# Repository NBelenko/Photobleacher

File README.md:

# Photobleacher

Photobleacher is an open-source photobleaching device designed to bleach autofluorescence and pigments in biological materials. For more details about the project, please refer to our [publication](https://doi.org/10.1101/2025.02.24.639965).

## About This Repository

This repository contains the following materials.

1. CAD file of the chassis (Enclosure CAD)
2. PCB board design (PCB)
3. Sample stage design (Sample Stage)
4. List of components (Main BOM.xlsx)
5. Wiring diagram (PB Block & Wiring Diagram.pdf)
6. Assembly instructions (PB_Assembly Instructions.pdf)

## Citation

> Murakami et al. Open-source Photobleacher for Fluorescent Imaging of Large Pigment-Rich Tissues. bioRxiv (2025) https://doi.org/10.1101/2025.02.24.639965 

## License

We provide this open source software without any warranty under the [MIT license](https://opensource.org/licenses/MIT).

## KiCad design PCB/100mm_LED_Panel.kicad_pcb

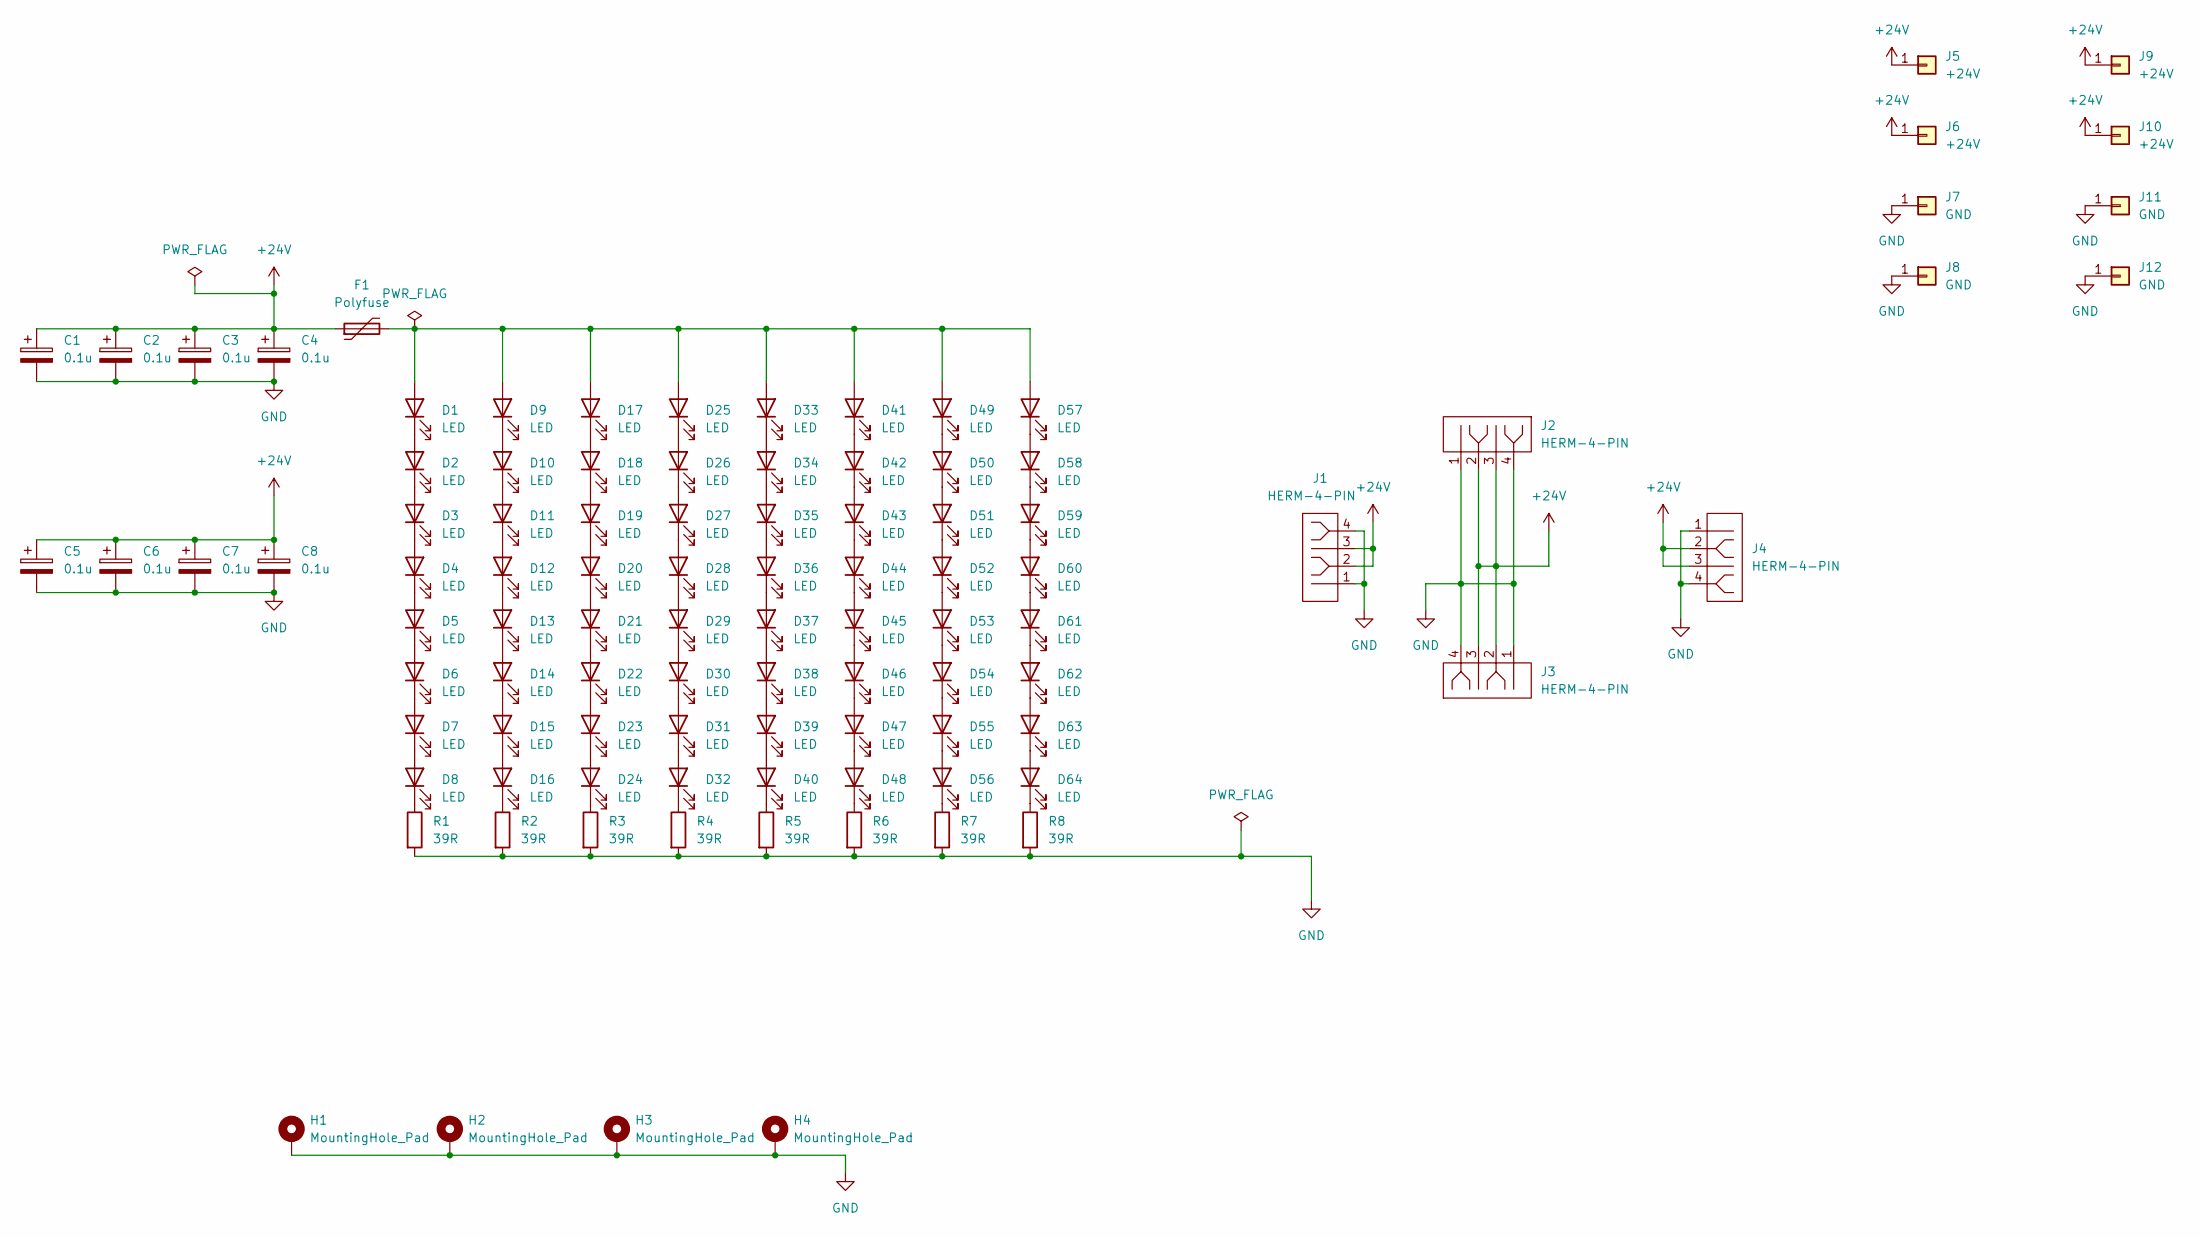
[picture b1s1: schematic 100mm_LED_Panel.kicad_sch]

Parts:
C1, C2, C3, C4, C5, C6, C7, C8: 0.1u; CP_EIA-3216-18_Kemet-A; Part Num T491A104K035AT; DigiKey P/N 399-3676-1-ND
D1, D2, D3, D4, D5, D6, D7, D8, D9, D10, D11, D12, D13, D14, D15, D16, D17, D18, D19, D20, D21, D22, D23, D24, D25, D26, D27, D28, D29, D30, D31, D32, D33, D34, D35, D36, D37, D38, D39, D40, D41, D42, D43, D44, D45, D46, D47, D48, D49, D50, D51, D52, D53, D54, D55, D56, D57, D58, D59, D60, D61, D62, D63, D64: LED; LED_Luminus_MP-3030-1100_3.0x3.0mm_Thermal-Vias; Part Num MP-3030-120H-30-80; DigiKey P/N 1214-MP-3030-120H-30-80CT-ND
F1: Polyfuse; Fuse_2018_5045Metric_Pad_HandSolder; Part Num DECASMDC050F/60-2; DigiKey P/N DECASMDC050F/60-2CT-ND
H1, H2, H3, H4: MountingHole_Pad; MountingHole_3.2mm_M3_Pad
J1, J2, J3, J4: HERM-4-PIN; TE 2213611-2 4 Position Mini-HERM; Part Num 2213611-2; DigiKey P/N A124894CT-ND
J5, J6, J9, J10: +24V; Faston .25 Tab; Part Num 63824-1; DigiKey P/N A29938CT-ND
J7, J8, J11, J12: GND; Faston .25 Tab; Part Num 63824-1; DigiKey P/N A29938CT-ND
R1, R2, R3, R4, R5, R6, R7, R8: 39R; R_1206_3216Metric_Pad1.30x1.75mm_HandSolder; Part Num RCS120639R0FKEA; DigiKey P/N 541-10632-1-ND

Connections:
+24V: C1.1, C2.1, C3.1, C4.1, C5.1, C6.1, C7.1, C8.1, F1.1, J1.2, J1.3, J2.2, J2.3, J3.2, J3.3, J4.2, J4.3, J5.1, J6.1, J9.1, J10.1
GND: C1.2, C2.2, C3.2, C4.2, C5.2, C6.2, C7.2, C8.2, H1.1, H2.1, H3.1, H4.1, J1.1, J1.4, J2.1, J2.4, J3.1, J3.4, J4.1, J4.4, J7.1, J8.1, J11.1, J12.1, R1.2, R2.2, R3.2, R4.2, R5.2, R6.2, R7.2, R8.2
unnamed: D1.1 (K), D2.2 (A)
unnamed: D1.2 (A), D9.2 (A), D17.2 (A), D25.2 (A), D33.2 (A), D41.2 (A), D49.2 (A), D57.2 (A), F1.2
unnamed: D2.1 (K), D3.2 (A)
unnamed: D3.1 (K), D4.2 (A)
unnamed: D4.1 (K), D5.2 (A)
unnamed: D5.1 (K), D6.2 (A)
unnamed: D6.1 (K), D7.2 (A)
unnamed: D7.1 (K), D8.2 (A)
unnamed: D8.1 (K), R1.1
unnamed: D10.1 (K), D11.2 (A)
unnamed: D9.1 (K), D10.2 (A)
unnamed: D11.1 (K), D12.2 (A)
unnamed: D12.1 (K), D13.2 (A)
unnamed: D13.1 (K), D14.2 (A)
unnamed: D14.1 (K), D15.2 (A)
unnamed: D15.1 (K), D16.2 (A)
unnamed: D16.1 (K), R2.1
unnamed: D17.1 (K), D18.2 (A)
unnamed: D18.1 (K), D19.2 (A)
unnamed: D19.1 (K), D20.2 (A)
unnamed: D20.1 (K), D21.2 (A)
unnamed: D21.1 (K), D22.2 (A)
unnamed: D22.1 (K), D23.2 (A)
unnamed: D23.1 (K), D24.2 (A)
unnamed: D24.1 (K), R3.1
unnamed: D25.1 (K), D26.2 (A)
unnamed: D26.1 (K), D27.2 (A)
unnamed: D27.1 (K), D28.2 (A)
unnamed: D28.1 (K), D29.2 (A)
unnamed: D29.1 (K), D30.2 (A)
unnamed: D30.1 (K), D31.2 (A)
unnamed: D31.1 (K), D32.2 (A)
unnamed: D32.1 (K), R4.1
unnamed: D33.1 (K), D34.2 (A)
unnamed: D34.1 (K), D35.2 (A)
unnamed: D35.1 (K), D36.2 (A)
unnamed: D36.1 (K), D37.2 (A)
unnamed: D37.1 (K), D38.2 (A)
unnamed: D38.1 (K), D39.2 (A)
unnamed: D39.1 (K), D40.2 (A)
unnamed: D40.1 (K), R5.1
unnamed: D41.1 (K), D42.2 (A)
unnamed: D42.1 (K), D43.2 (A)
unnamed: D43.1 (K), D44.2 (A)
unnamed: D44.1 (K), D45.2 (A)
unnamed: D45.1 (K), D46.2 (A)
unnamed: D46.1 (K), D47.2 (A)
unnamed: D47.1 (K), D48.2 (A)
unnamed: D48.1 (K), R6.1
unnamed: D49.1 (K), D50.2 (A)
unnamed: D50.1 (K), D51.2 (A)
unnamed: D51.1 (K), D52.2 (A)
unnamed: D52.1 (K), D53.2 (A)
unnamed: D53.1 (K), D54.2 (A)
unnamed: D54.1 (K), D55.2 (A)
unnamed: D55.1 (K), D56.2 (A)
unnamed: D56.1 (K), R7.1
unnamed: D57.1 (K), D58.2 (A)
unnamed: D58.1 (K), D59.2 (A)
unnamed: D59.1 (K), D60.2 (A)
unnamed: D60.1 (K), D61.2 (A)
unnamed: D61.1 (K), D62.2 (A)
unnamed: D62.1 (K), D63.2 (A)
unnamed: D63.1 (K), D64.2 (A)
unnamed: D64.1 (K), R8.1

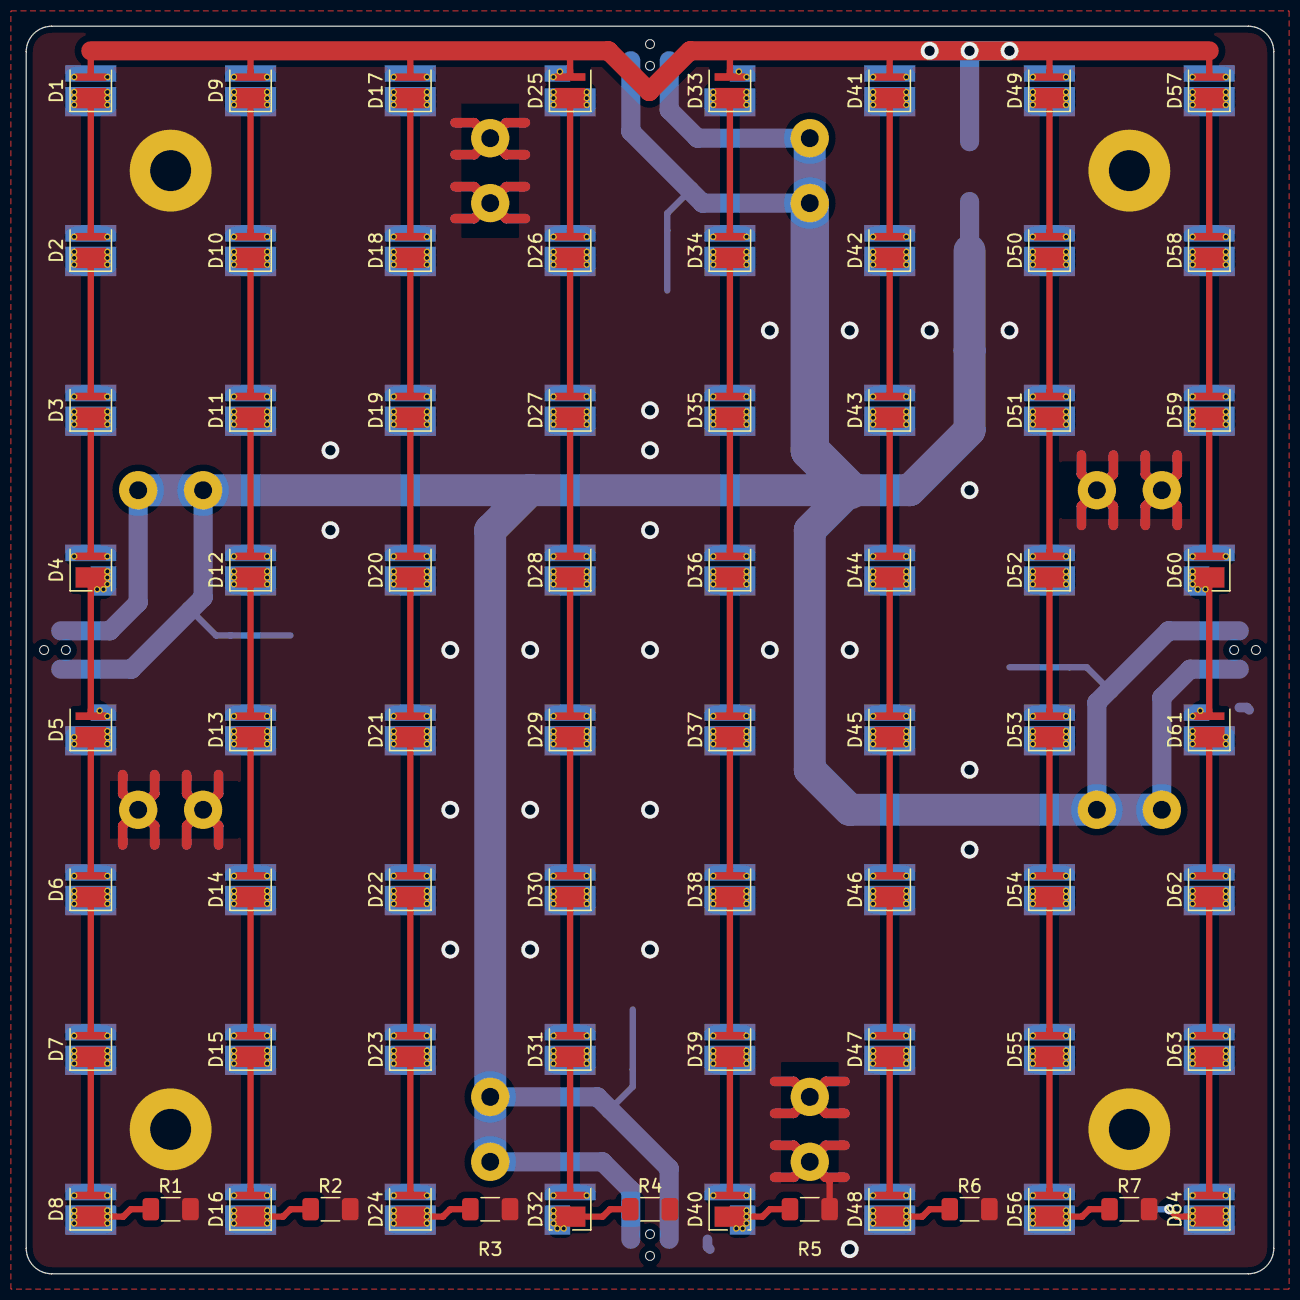
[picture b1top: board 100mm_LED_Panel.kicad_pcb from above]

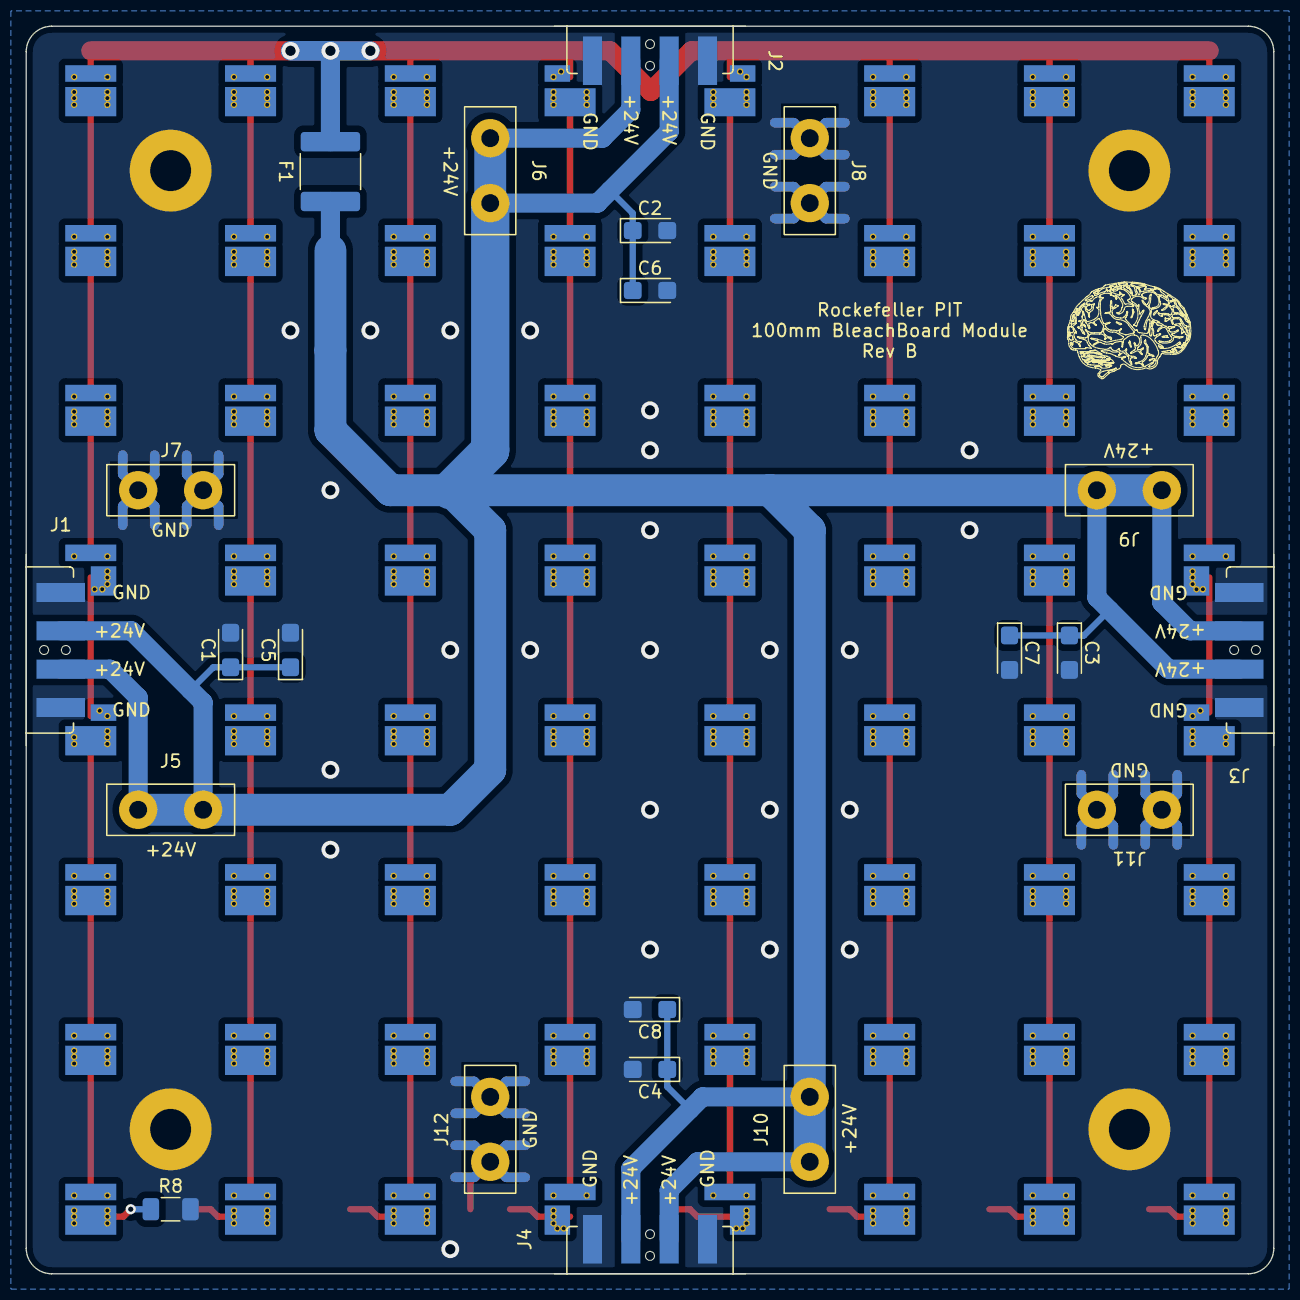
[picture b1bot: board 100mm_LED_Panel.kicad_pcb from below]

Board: 2 copper layers, 97.6 x 97.6 mm, 97 parts (22 on the bottom side), 67 nets.

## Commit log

2024-12-17 PCB Files
    Board, Schematic, and gerber files for fabrication for the LED panel PCB
2024-12-17 Create 100mm_LED_Panel
2024-12-17 Create 100mm_LED_Panel-RevB
2024-12-17 Create stage
2025-02-24 Create LICENSE
2025-02-24 Added CAD directory/main STEP file
2025-03-17 Main BOM Cleanup
2025-03-24 edit readme
